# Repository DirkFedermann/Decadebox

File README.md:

# Decadebox
Schematic and PCB files for a decade box for electronic prototyping.

Base of it is a Decimal/BCD Pushwheel switch from Aliexpress.
Search terms you might want to try are: `Decimal` `BCD` `Pushwheel` `switch` `KM1`
There are AFAIK 3 sizes. These PCBs are made for the middle size KM1.

BCD (Binary-coded decimal) version is used for a capacitor decade box.
Decimal version is used for a resistor decade box.

All files a made using [Kicad](https://www.kicad.org/)
and Gerber files are exported for [JLCPCB](https://jlcpcb.com/) with the option "Remove Order Number" to "Specify a location".

# These PCBs have not been tested yet!
Double check if you want to use them, before ordering.

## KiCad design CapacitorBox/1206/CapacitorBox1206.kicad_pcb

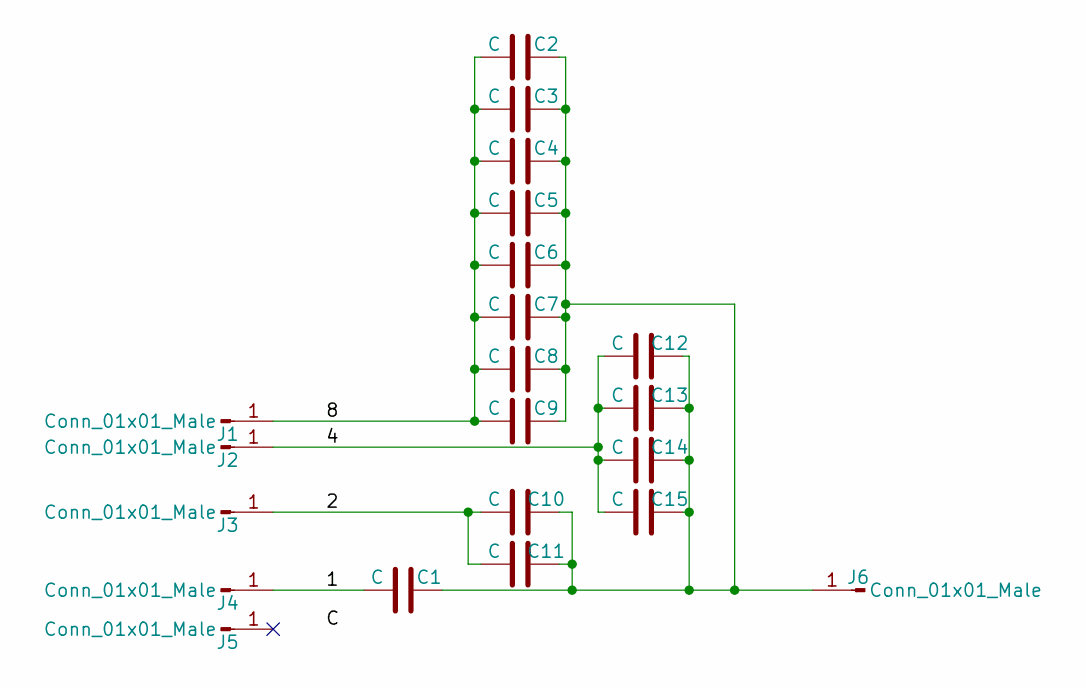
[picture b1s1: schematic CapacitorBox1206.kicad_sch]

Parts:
C1, C2, C3, C4, C5, C6, C7, C8, C9, C10, C11, C12, C13, C14, C15: C; C_1206_3216Metric_Pad1.33x1.80mm_HandSolder
J1, J2, J3, J4, J5, J6: Conn_01x01_Male; PinHeader_1x01_P2.54mm_Vertical

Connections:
/1: C1.1, J4.1
/2: C10.1, C11.1, J3.1
/4: C12.1, C13.1, C14.1, C15.1, J2.1
/8: C2.1, C3.1, C4.1, C5.1, C6.1, C7.1, C8.1, C9.1, J1.1
unnamed: C1.2, C2.2, C3.2, C4.2, C5.2, C6.2, C7.2, C8.2, C9.2, C10.2, C11.2, C12.2, C13.2, C14.2, C15.2, J6.1

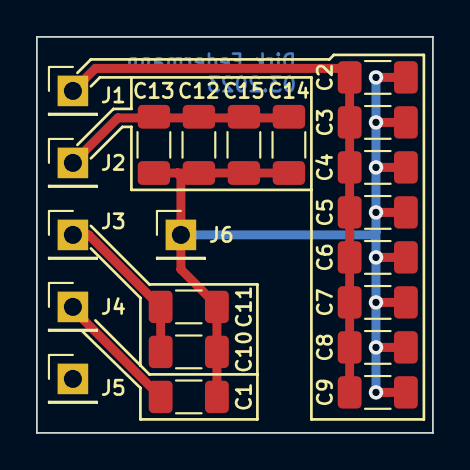
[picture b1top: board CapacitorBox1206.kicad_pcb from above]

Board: 2 copper layers, 22.0 x 22.0 mm, 21 parts (0 on the bottom side), 5 nets.

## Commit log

2023-03-10 Added CapacitorBox initial commit
